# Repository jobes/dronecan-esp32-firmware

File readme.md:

# InSkyCore DroneCAN Firmware Platform

Low-cost ESP32-based avionics devices for experimental aviation.

This repository is a multi-firmware platform for building DroneCAN nodes and sensors for:

- experimental and ultralight airplanes
- powered hang gliders
- custom cockpit projects

The practical goal is simple: publish important flight and engine data over DroneCAN so the pilot can see everything critical on a tablet in the cockpit.

## Vision

This project focuses on:

- affordable hardware built around ESP32
- reusable DroneCAN software components
- multiple device firmwares in one repository
- fast iteration for real-world flying needs

## Safety Notice

This project is intended for experimental use.

It is not a certified avionics system and must not be treated as the sole source of flight-critical information. Always keep independent, appropriate backup instrumentation.

## Repository Layout

```text
firmware/
	components/                  # Shared ESP-IDF components used by all firmwares
		dronecan_mini/             # DroneCAN communication, node state, params, FW update
		bmp3_sensor_api/           # BMP3/BMP390 sensor integration component
		libcanard/                 # ESP-IDF wrapper/component for libcanard

	firmwares/
		<firmware-name>/           # Individual firmware projects (each has its own README)

	submodules/
		libcanard/                 # Upstream libcanard submodule
		bmp3_sensor_api/           # Upstream BMP3 sensor API submodule
```

## Firmware-Specific Documentation

Each firmware under `firmwares/` has (or should have) its own `readme.md` with:

- hardware details and pinout
- published DroneCAN messages/services
- target MCU and board notes
- exact build/flash commands
- calibration and test notes

## Requirements

- Linux development environment
- ESP-IDF installed (compatible with your project setup)
- USB access to target board
- CAN transceiver and proper wiring for DroneCAN bus

## Quick Start

Clone with submodules:

```bash
git clone --recurse-submodules <REPO_URL>
cd firmware
```

If already cloned, update submodules:

```bash
git submodule update --init --recursive
```

Load ESP-IDF environment:

```bash
. /opt/esp-idf/export.sh
```

Build and flash a selected firmware:

```bash
cd firmwares/<firmware-name>
# Follow target selection and configuration in that firmware's readme.md
idf.py -p /dev/ttyACM1 build flash monitor
```

## How To Add a New Device Firmware

1. Create a new folder under `firmwares/`.
2. Add a standard ESP-IDF project (`CMakeLists.txt`, `main/`, config files).
3. Reuse shared logic from `../../components` (especially `dronecan_mini`).
4. Define per-device settings in `main/project_config.h`.
5. Add sensor/application code in `main/` and publish required DroneCAN topics.
6. Build, flash, and validate on a real CAN bus.

## Design Principles

- Keep common DroneCAN logic in shared components.
- Keep firmware-specific hardware details in each firmware folder.
- Prefer explicit parameters for in-field calibration.
- Optimize for robustness and predictable behavior over features.

## Roadmap Ideas

- additional air-data and environmental sensors
- engine monitoring nodes (EGT/CHT, RPM, pressures)
- electrical system telemetry (voltage/current/battery)
- GPS/attitude helper nodes for glass-cockpit integration
- standardized tablet-friendly data profiles

## Contribution

Contributions and practical flight-test feedback are welcome.

Recommended contribution style:

- keep commits focused and small
- document pinout/protocol assumptions
- include test notes (bench or flight context)

## License

Add the project license information here (for example MIT, BSD, or GPL) once finalized.

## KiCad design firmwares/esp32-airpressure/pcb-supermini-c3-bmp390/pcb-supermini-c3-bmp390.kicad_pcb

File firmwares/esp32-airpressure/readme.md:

# ESP32 Air Pressure Firmware

Firmware for an ESP32-C3 based DroneCAN air data node using a BMP390 pressure sensor over SPI.

## What This Firmware Does

- Initializes the BMP390 sensor over SPI.
- Joins DroneCAN network over TWAI/CAN.
- Uses DroneCAN dynamic node ID allocation at startup.
- Publishes:
  - `uavcan.equipment.air_data.StaticPressure` (type ID `1028`)
  - `uavcan.equipment.air_data.StaticTemperature` (type ID `1029`)
- Publishes heartbeat (`uavcan.protocol.NodeStatus`) approximately every `950 ms`.
- Exposes runtime parameters for pressure and temperature offsets.

## Hardware Configuration

Defined in `main/project_config.h`.

### CAN (TWAI)

- `CAN_TX_PIN`: `GPIO21`
- `CAN_RX_PIN`: `GPIO20`
- Bitrate: `1 Mbit/s` (`TWAI_TIMING_CONFIG_1MBITS`)

Note: ESP32-C3 requires an external CAN transceiver between MCU TWAI pins and CAN bus.

### BMP390 (SPI)

- `BMP_SCLK`: `GPIO4`
- `BMP_MISO`: `GPIO5`
- `BMP_MOSI`: `GPIO6`
- `BMP_CS`: `GPIO7`
- SPI clock: `1 MHz`

## DroneCAN Node Behavior

- Node starts in `MODE_INITIALIZATION`.
- During startup it requests a dynamic node ID using its unique ID.
- After successful initialization, application switches to `MODE_OPERATIONAL`.
- Main loop period is `100 ms`.
- If sensor read or publish fails, node health is degraded (`WARNING/ERROR/CRITICAL` depending on failure).

## Runtime Parameters

The node registers two float parameters (available over DroneCAN param services):

- `pressure_offset`
  - Range: `-100.0 .. 100.0`
  - Default: `0.0`
  - Applied to published pressure in pascals.
- `temp_offset`
  - Range: `-10.0 .. 10.0`
  - Default: `0.0`
  - Applied to published temperature in degrees Celsius.

Parameters are backed by NVS and can be saved/erased through standard DroneCAN parameter opcodes.

## Build and Flash

From repository root:

```bash
. /opt/esp-idf/export.sh
cd firmwares/esp32-airpressure
# idf.py set-target esp32c3 already set
idf.py -p /dev/ttyACM1 build flash monitor
```

If target is already set, you can skip `set-target`.

## Useful Commands

```bash
# Build only
idf.py build

# Flash only
idf.py -p /dev/ttyACM1 flash

# Monitor only
idf.py -p /dev/ttyACM1 monitor
```

## Project Structure Notes

- Shared components are taken from `../../components`.
- Shared submodules are located in `../../submodules`.
- Partition table is defined in `partitions.csv` (OTA slots + SPIFFS storage).

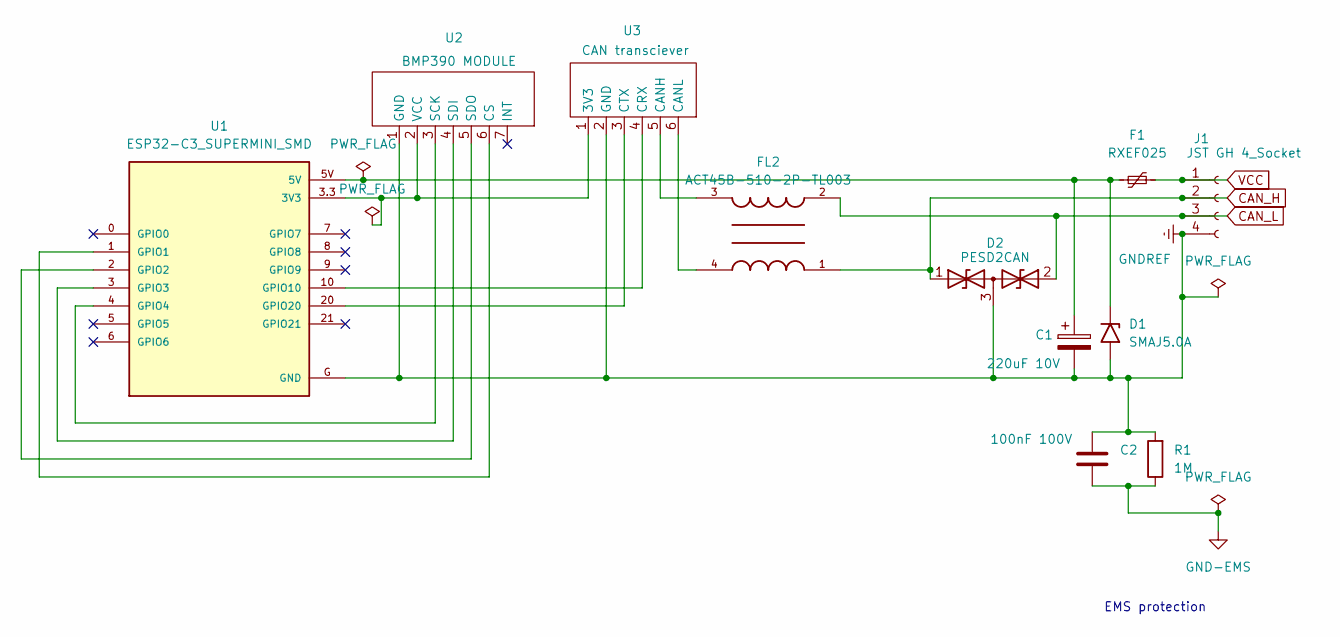
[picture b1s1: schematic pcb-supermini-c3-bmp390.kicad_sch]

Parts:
C1: 220uF 10V; CP_Radial_D5.0mm_P2.00mm
C2: 100nF 100V; C_Rect_L7.2mm_W3.0mm_P5.00mm_FKS2_FKP2_MKS2_MKP2
D1: SMAJ5.0A; D_SMA
D2: PESD2CAN; SOT-23-3
F1: RXEF025; C_Disc_D4.7mm_W2.5mm_P5.00mm
FL2: ACT45B-510-2P-TL003; FIL_ACT45B-510-2P-TL003; PARTREV 20200405
J1: JST GH 4_Socket; JST_GH_SM04B-GHS-TB_1x04-1MP_P1.25mm_Horizontal
R1: 1M; R_Axial_DIN0207_L6.3mm_D2.5mm_P10.16mm_Horizontal
U1: ESP32-C3_SUPERMINI_SMD; MODULE_ESP32-C3_SUPERMINI
U2: BMP390 MODULE; BMP390_Module
U3: CAN transciever; CAN_Module

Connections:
CAN_H: D2.1 (A1), FL2.1, J1.2
CAN_L: D2.2 (A2), FL2.2, J1.3
GND-EMS: C2.2, R1.1
GNDREF: C1.2, C2.1, D1.2 (A2), D2.3 (common), J1.4, R1.2, U1.G (GND), U2.1 (GND), U3.2 (GND)
unnamed: C1.1, D1.1 (A1), F1.1, U1.5V
unnamed: U1.3.3 (3V3), U2.2 (VCC), U3.1 (3V3)
unnamed: U1.1 (GPIO1), U2.6 (CS)
unnamed: U1.2 (GPIO2), U2.5 (SDO)
unnamed: U1.3 (GPIO3), U2.4 (SDI)
unnamed: U1.4 (GPIO4), U2.3 (SCK)
unnamed: U1.10 (GPIO10), U3.4 (CRX)
unnamed: U1.20 (GPIO20), U3.3 (CTX)
unnamed: FL2.3, U3.5 (CANH)
unnamed: FL2.4, U3.6 (CANL)
VCC: F1.2, J1.1

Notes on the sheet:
EMS protection

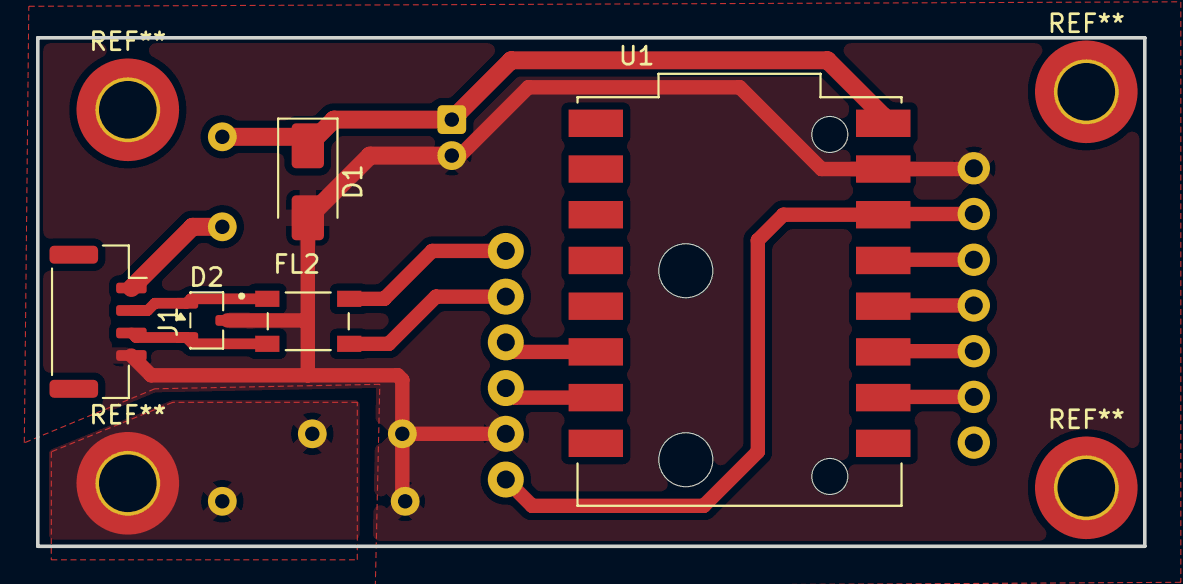
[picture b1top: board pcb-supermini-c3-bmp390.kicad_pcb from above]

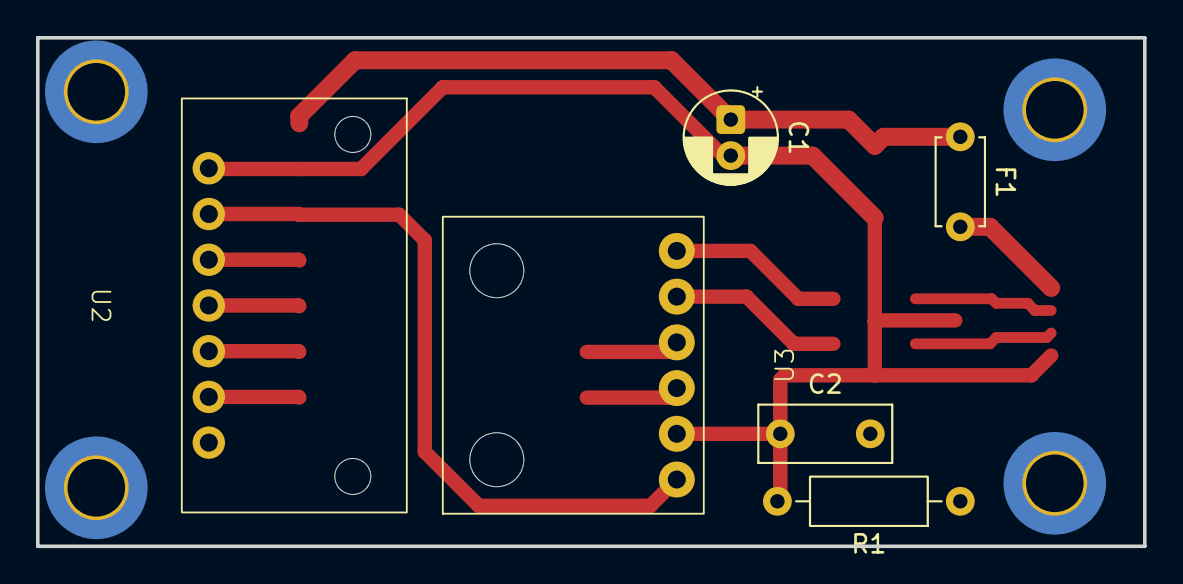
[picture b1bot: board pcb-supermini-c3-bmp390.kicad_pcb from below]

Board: 2 copper layers, 61.5 x 28.2 mm, 11 parts (6 on the bottom side), 15 nets.

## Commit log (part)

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2026-02-19 init
2026-02-19 first compiled output
2026-02-19 first working test
2026-02-19 remove unneeded variables
2026-02-20 add BMP390 sensor integration and update project configuration
2026-02-20 add static pressure publishing to DroneCAN and update broadcast function
2026-02-20 move pressure message to own file
2026-02-20 move everything non app logic from main.c out
2026-02-20 add StaticTemperature message handling and integrate temperature publishing
2026-02-20 add app_tasks and restructure DroneCAN node management
2026-02-20 refactor DroneCAN node to handle GetNodeInfo response and improve message management
2026-02-21 add RestartNode message handling and implement restart functionality
2026-02-22 get parameter configuration
2026-02-22 device parameters load from nvm, but can be changed via can
2026-02-22 Implement parameter change notification and refactor device parameter handling
2026-02-22 add support for saving params to non volatile memory
2026-02-25 firmware update over CAN
2026-02-28 add support for dynamic node id
2026-03-02 Enable application rollback and OTA rollback functionality
2026-03-02 Add GetTransportStats message support and related functions
2026-03-02 Implement node restart functionality with delayed execution and update response handling
2026-03-09 refactoring
2026-03-09 refactor
2026-03-09 make library style so we can have more firmware
2026-03-10 update sdkconfig for ESP-IDF 5.5.3 and add new configuration options
2026-03-10 update readme to clarify that target for esp32c3 is already set
2026-03-19 Add symbol library and components for BMP390 and CAN transceiver
    - Created a new symbol library file for the ESP32-C3 Supermini project.
    - Added symbols for BMP390 module and CAN transceiver with their respective properties and pin configurations.
    - Included necessary metadata for the symbol library to ensure compatibility with KiCad.
2026-03-20 refactor: update PCB to be on 2 layers
2026-03-20 chore: Update libcanard core, drivers, tests, examples, C++ wrappers, and build configurations.
2026-03-27 feat: Add new ESP32 air pressure sensor PCB design
2026-03-28 Refactor code structure for improved readability and maintainability
2026-03-28 esp32-gateway empty basic empty firmware
2026-03-28 feat: Implement Wi-Fi manager and device parameter retrieval functions
2026-03-28 feat: Add HTTP server and mDNS service for device discovery
2026-03-28 feat: Advertise Cannelloni service for CAN bus tunneling in mDNS
2026-03-28 chore: update libcanard submodule and add firmware workflow documentation
2026-05-03 Refactor ESP32 Gateway Firmware
    - Updated main.c to include cannelloni_bridge and improved task management.
    - Modified project_config.h to change CAN TX/RX pins and added Cannelloni configuration parameters.
    - Added new HTML files for station mode configuration, device status, and system settings.
    - Created a template HTML file for consistent UI styling across the web interface.
    - Enhanced wifi_manager.c to improve WiFi connection handling and added support for Cannelloni services.
    - Updated sdkconfig to set the CPU frequency to 240 MHz for better performance.
2026-05-03 fix: streamline CAN frame transmission and update ESP-IDF version to 6.0.1
2026-05-03 feat: enhance unique ID logging and adjust CAN message encoding for unique ID
2026-05-04 fix: improve error handling in CAN frame processing and update Cannelloni frame size definitions
2026-05-05 Add DroneCAN Node Monitoring and Update Web Interface
    - Introduced dronecan_node_monitor.h for managing DroneCAN node information.
    - Updated http_server.c to handle new routes for nodes and status APIs.
    - Implemented new HTML pages for displaying node information and device status.
    - Added JavaScript for dynamic updates of node data and device uptime.
    - Created CSS styles for improved UI presentation of node information.
    - Removed outdated HTML files related to STA and system settings.
2026-05-05 fix: replace xTaskGetTickCount with esp_timer_get_time for accurate time tracking
2026-05-05 Add Data Monitor functionality with HTML, CSS, and JavaScript support
    - Introduced dronecan_data_monitor.c and dronecan_data_monitor.h for managing data subscriptions and processing transfers.
    - Updated CMakeLists.txt to include new source files and web assets for the data monitor.
    - Created monitor.html for the user interface of the data monitor, allowing users to add and manage monitors.
    - Developed monitor.css for styling the data monitor interface, ensuring a responsive and user-friendly design.
    - Implemented monitor.js to handle the logic for adding, deleting, and displaying monitor data, including fetching data from the server.
    - Enhanced http_server.c to serve the new monitor page and
2026-05-20 feat: fix and enhance dynamic node ID allocation with preferred ID handling
2026-05-20 fix: when STA not set, html for setting it was without inputs
2026-06-17 Enhance PCB configuration and add new holders
    - Updated PCB project settings in `pcb-supermini-c3-bmp390.kicad_pro` to improve zone parameters and error handling.
    - Introduced new annotation settings for schematic management.
    - Added `under-bmp390-holder.FCStd` and `under-can-holder.FCStd` files for component support.
